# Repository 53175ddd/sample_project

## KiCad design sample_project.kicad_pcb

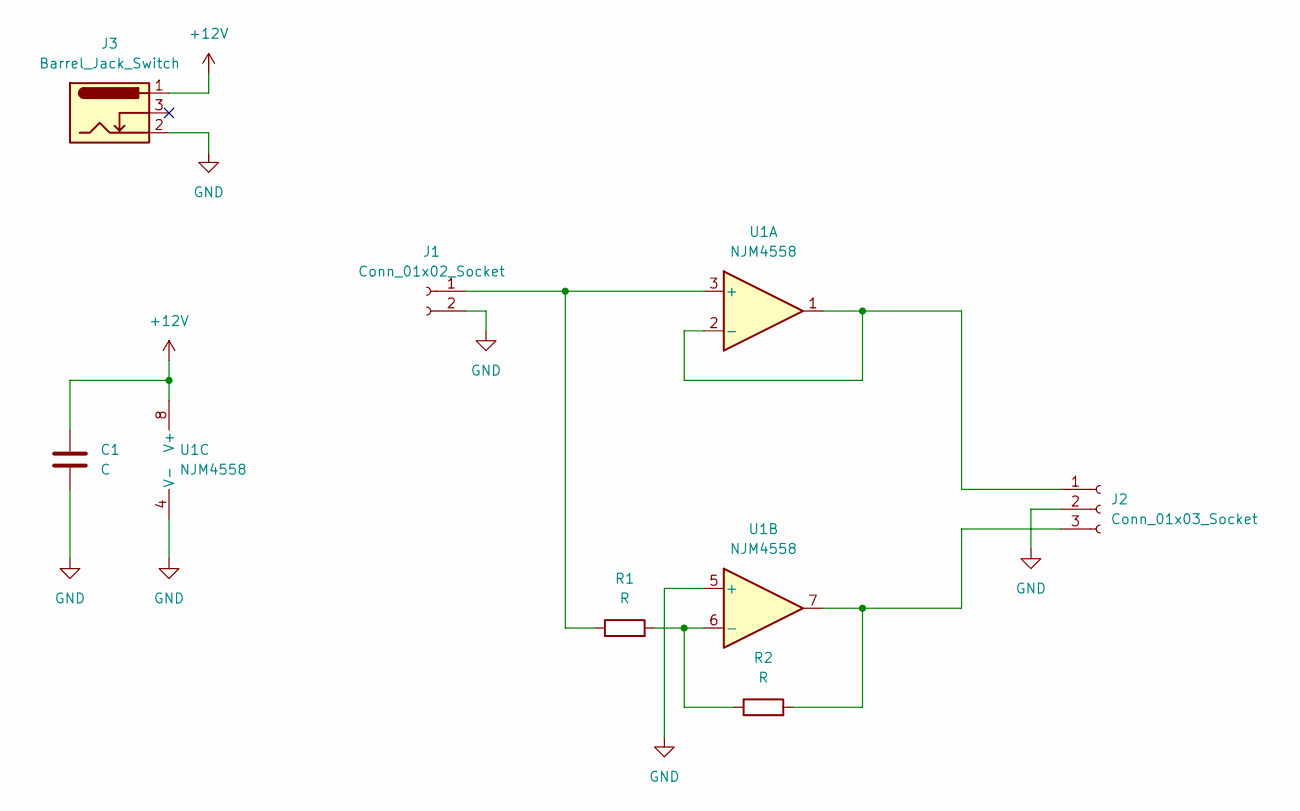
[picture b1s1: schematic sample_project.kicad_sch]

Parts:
C1: C; C_Disc_D5.0mm_W2.5mm_P5.00mm
J1: Conn_01x02_Socket; PinSocket_1x02_P2.54mm_Vertical
J2: Conn_01x03_Socket; PinSocket_1x03_P2.54mm_Vertical
J3: Barrel_Jack_Switch; BarrelJack_Horizontal
R1, R2: R; R_Axial_DIN0207_L6.3mm_D2.5mm_P10.16mm_Horizontal
U1: NJM4558; DIP-8_W7.62mm

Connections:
+12V: C1.1, J3.1, U1.8 (V+)
GND: C1.2, J1.2, J2.2, J3.2, U1.4 (V-), U1.5 (+)
unnamed: J1.1, R1.1, U1.3 (+)
unnamed: J2.1, U1.1, U1.2 (-)
unnamed: J2.3, R2.2, U1.7
unnamed: R1.2, R2.1, U1.6 (-)

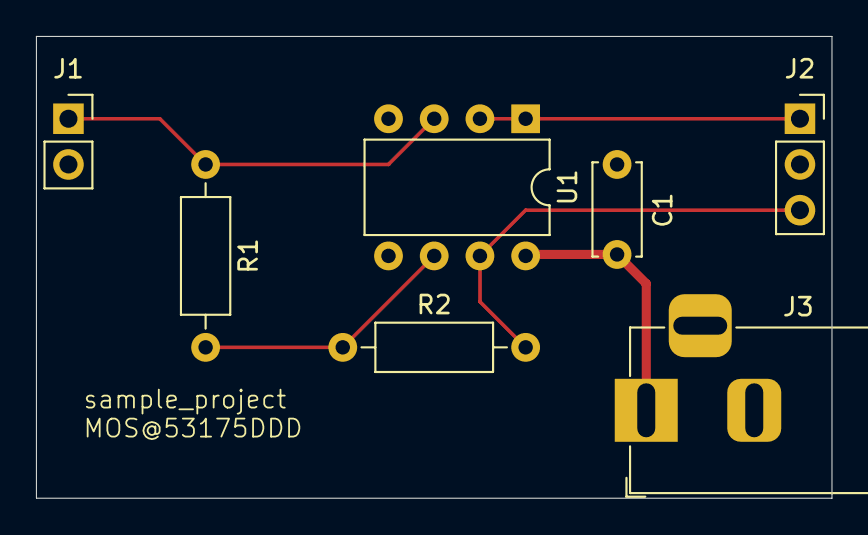
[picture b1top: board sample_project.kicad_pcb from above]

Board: 2 copper layers, 44.2 x 25.7 mm, 7 parts (0 on the bottom side), 6 nets.

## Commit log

2024-11-05 ファイル作成
2024-11-05 回路作成
2024-11-05 フットプリント割り当て
2024-11-05 基板作成
